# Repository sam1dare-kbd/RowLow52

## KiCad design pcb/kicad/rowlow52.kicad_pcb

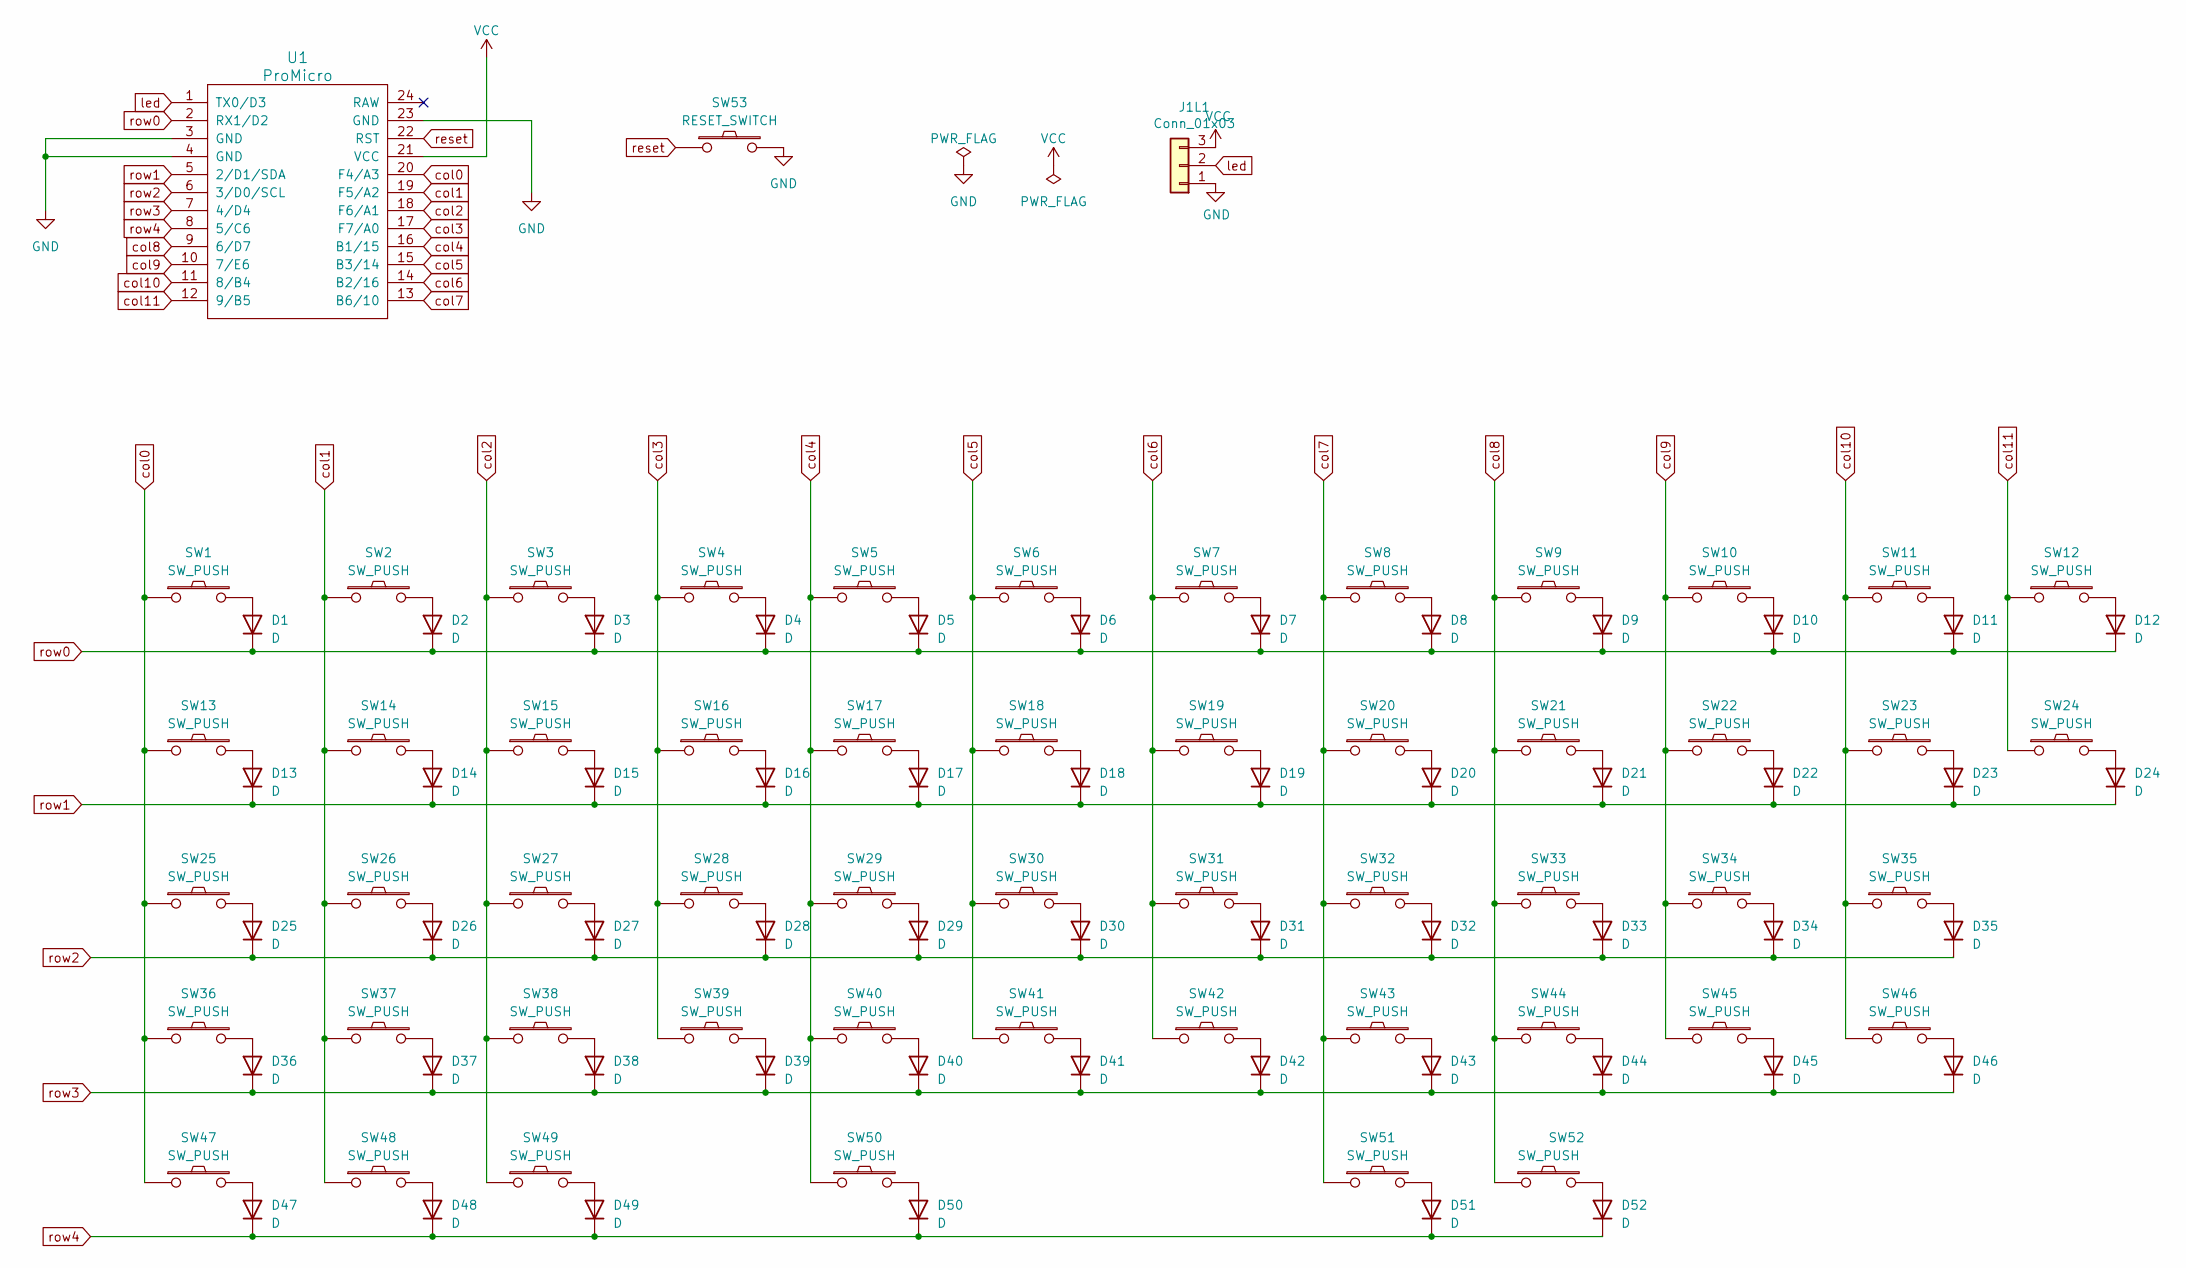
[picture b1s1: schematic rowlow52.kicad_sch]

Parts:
D1, D2, D3, D4, D5, D6, D7, D8, D9, D10, D11, D12, D13, D14, D15, D16, D17, D18, D19, D20, D21, D22, D23, D24, D25, D26, D27, D28, D29, D30, D31, D32, D33, D34, D35, D36, D37, D38, D39, D40, D41, D42, D43, D44, D45, D46, D47, D48, D49, D50, D51, D52: D; D3_TH_SMD
J1L1: Conn_01x03; StripLED_rev
SW1, SW2, SW3, SW4, SW5, SW6, SW7, SW8, SW9, SW10, SW11, SW14, SW15, SW16, SW17, SW18, SW19, SW20, SW21, SW22, SW23, SW24, SW26, SW27, SW28, SW29, SW30, SW31, SW32, SW33, SW34, SW37, SW38, SW39, SW40, SW41, SW42, SW43, SW44, SW45, SW48, SW49: SW_PUSH; CherryMX_Hotswap_1u
SW12, SW13, SW46, SW47, SW51: SW_PUSH; CherryMX_Hotswap_1.25u
SW25, SW52: SW_PUSH; CherryMX_Hotswap_1.5u
SW35: SW_PUSH; CherryMX_Hotswap_1.75u
SW36: SW_PUSH; CherryMX_Hotswap_2u
SW50: SW_PUSH; CherryMX_Hotswap_6.25u
SW53: RESET_SWITCH; ResetSW_1side
U1: ProMicro; ProMicro_v2_1side

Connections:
GND: J1L1.1, SW53.2, U1.3 (GND), U1.4 (GND), U1.23 (GND)
unnamed: D1.2 (A), SW1.2
unnamed: D2.2 (A), SW2.2
unnamed: D3.2 (A), SW3.2
unnamed: D4.2 (A), SW4.2
unnamed: D5.2 (A), SW5.2
unnamed: D6.2 (A), SW6.2
unnamed: D7.2 (A), SW7.2
unnamed: D8.2 (A), SW8.2
unnamed: D9.2 (A), SW9.2
unnamed: D10.2 (A), SW10.2
unnamed: D11.2 (A), SW11.2
unnamed: D12.2 (A), SW12.2
unnamed: D13.2 (A), SW13.2
unnamed: D14.2 (A), SW14.2
unnamed: D15.2 (A), SW15.2
unnamed: D16.2 (A), SW16.2
unnamed: D17.2 (A), SW17.2
unnamed: D18.2 (A), SW18.2
unnamed: D19.2 (A), SW19.2
unnamed: D20.2 (A), SW20.2
unnamed: D21.2 (A), SW21.2
unnamed: D22.2 (A), SW22.2
unnamed: D23.2 (A), SW23.2
unnamed: D24.2 (A), SW24.2
unnamed: D25.2 (A), SW25.2
unnamed: D26.2 (A), SW26.2
unnamed: D27.2 (A), SW27.2
unnamed: D28.2 (A), SW28.2
unnamed: D29.2 (A), SW29.2
unnamed: D30.2 (A), SW30.2
unnamed: D31.2 (A), SW31.2
unnamed: D32.2 (A), SW32.2
unnamed: D33.2 (A), SW33.2
unnamed: D34.2 (A), SW34.2
unnamed: D35.2 (A), SW35.2
unnamed: D36.2 (A), SW36.2
unnamed: D37.2 (A), SW37.2
unnamed: D38.2 (A), SW38.2
unnamed: D39.2 (A), SW39.2
unnamed: D40.2 (A), SW40.2
unnamed: D41.2 (A), SW41.2
unnamed: D42.2 (A), SW42.2
unnamed: D43.2 (A), SW43.2
unnamed: D44.2 (A), SW44.2
unnamed: D45.2 (A), SW45.2
unnamed: D46.2 (A), SW46.2
unnamed: D47.2 (A), SW47.2
unnamed: D48.2 (A), SW48.2
unnamed: D49.2 (A), SW49.2
unnamed: D50.2 (A), SW50.2
unnamed: D51.2 (A), SW51.2
unnamed: D52.2 (A), SW52.2
VCC: J1L1.3, U1.21 (VCC)
col0: SW1.1, SW13.1, SW25.1, SW36.1, SW47.1, U1.20 (F4/A3)
col1: SW2.1, SW14.1, SW26.1, SW37.1, SW48.1, U1.19 (F5/A2)
col2: SW3.1, SW15.1, SW27.1, SW38.1, SW49.1, U1.18 (F6/A1)
col3: SW4.1, SW16.1, SW28.1, SW39.1, U1.17 (F7/A0)
col4: SW5.1, SW17.1, SW29.1, SW40.1, SW50.1, U1.16 (B1/15)
col5: SW6.1, SW18.1, SW30.1, SW41.1, U1.15 (B3/14)
col6: SW7.1, SW19.1, SW31.1, SW42.1, U1.14 (B2/16)
col7: SW8.1, SW20.1, SW32.1, SW43.1, SW51.1, U1.13 (B6/10)
col8: SW9.1, SW21.1, SW33.1, SW44.1, SW52.1, U1.9 (6/D7)
col9: SW10.1, SW22.1, SW34.1, SW45.1, U1.10 (7/E6)
col10: SW11.1, SW23.1, SW35.1, SW46.1, U1.11 (8/B4)
col11: SW12.1, SW24.1, U1.12 (9/B5)
led: J1L1.2, U1.1 (TX0/D3)
reset: SW53.1, U1.22 (RST)
row0: D1.1 (K), D2.1 (K), D3.1 (K), D4.1 (K), D5.1 (K), D6.1 (K), D7.1 (K), D8.1 (K), D9.1 (K), D10.1 (K), D11.1 (K), D12.1 (K), U1.2 (RX1/D2)
row1: D13.1 (K), D14.1 (K), D15.1 (K), D16.1 (K), D17.1 (K), D18.1 (K), D19.1 (K), D20.1 (K), D21.1 (K), D22.1 (K), D23.1 (K), D24.1 (K), U1.5 (2/D1/SDA)
row2: D25.1 (K), D26.1 (K), D27.1 (K), D28.1 (K), D29.1 (K), D30.1 (K), D31.1 (K), D32.1 (K), D33.1 (K), D34.1 (K), D35.1 (K), U1.6 (3/D0/SCL)
row3: D36.1 (K), D37.1 (K), D38.1 (K), D39.1 (K), D40.1 (K), D41.1 (K), D42.1 (K), D43.1 (K), D44.1 (K), D45.1 (K), D46.1 (K), U1.7 (4/D4)
row4: D47.1 (K), D48.1 (K), D49.1 (K), D50.1 (K), D51.1 (K), D52.1 (K), U1.8 (5/C6)

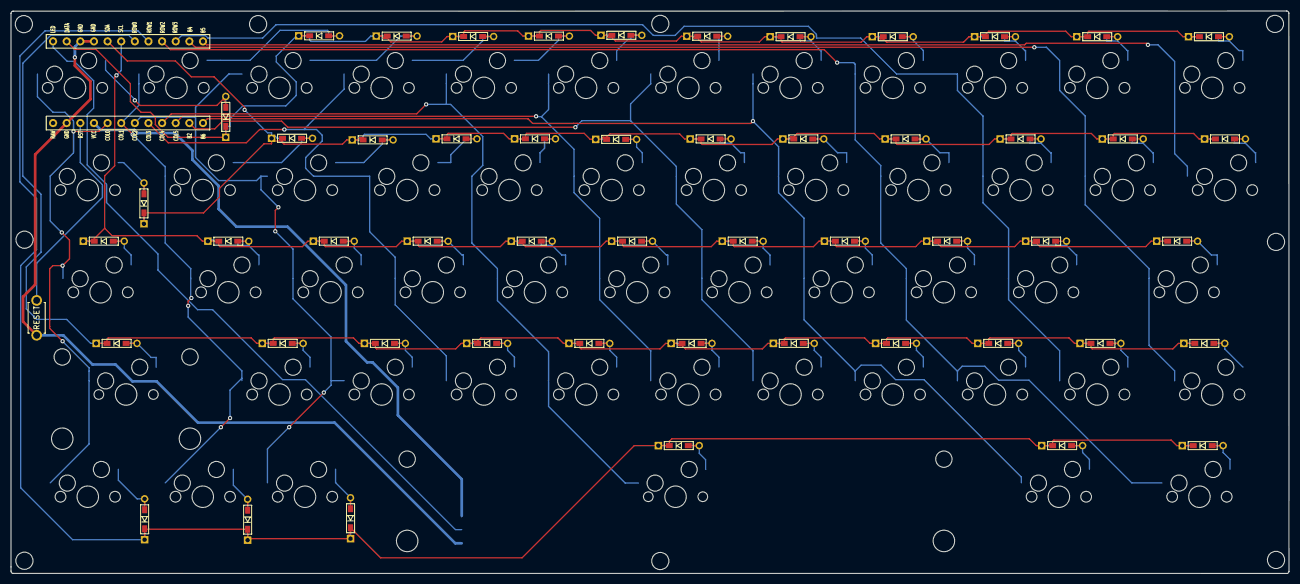
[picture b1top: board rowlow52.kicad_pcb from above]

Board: 2 copper layers, 238.2 x 104.8 mm, 116 parts (1 on the bottom side), 73 nets.

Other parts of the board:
Ref00, Ref01, Ref02, Ref03, Ref04, Ref05, Ref06, Ref07, Ref08: Val**; m3_Screw_Hole_EdgeCuts

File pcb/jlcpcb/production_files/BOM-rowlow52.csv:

Comment,Designator,Footprint,LCSC
SW_PUSH,SW23,CherryMX_Hotswap_1u,
D,D29,D3_TH_SMD,
D,D3,D3_TH_SMD,
D,D39,D3_TH_SMD,
SW_PUSH,SW3,CherryMX_Hotswap_1u,
D,D33,D3_TH_SMD,
D,D6,D3_TH_SMD,
SW_PUSH,SW8,CherryMX_Hotswap_1u,
SW_PUSH,SW39,CherryMX_Hotswap_1u,
D,D20,D3_TH_SMD,
D,D9,D3_TH_SMD,
D,D52,D3_TH_SMD,
SW_PUSH,SW32,CherryMX_Hotswap_1u,
D,D18,D3_TH_SMD,
D,D48,D3_TH_SMD,
SW_PUSH,SW35,CherryMX_Hotswap_1.75u,
D,D38,D3_TH_SMD,
SW_PUSH,SW6,CherryMX_Hotswap_1u,
D,D24,D3_TH_SMD,
SW_PUSH,SW19,CherryMX_Hotswap_1u,
D,D45,D3_TH_SMD,
SW_PUSH,SW43,CherryMX_Hotswap_1u,
D,D40,D3_TH_SMD,
SW_PUSH,SW30,CherryMX_Hotswap_1u,
D,D23,D3_TH_SMD,
SW_PUSH,SW13,CherryMX_Hotswap_1.25u,
SW_PUSH,SW28,CherryMX_Hotswap_1u,
D,D43,D3_TH_SMD,
SW_PUSH,SW42,CherryMX_Hotswap_1u,
D,D46,D3_TH_SMD,
SW_PUSH,SW16,CherryMX_Hotswap_1u,
SW_PUSH,SW15,CherryMX_Hotswap_1u,
SW_PUSH,SW41,CherryMX_Hotswap_1u,
SW_PUSH,SW44,CherryMX_Hotswap_1u,
SW_PUSH,SW47,CherryMX_Hotswap_1.25u,
SW_PUSH,SW4,CherryMX_Hotswap_1u,
SW_PUSH,SW40,CherryMX_Hotswap_1u,
SW_PUSH,SW50,CherryMX_Hotswap_6.25u,
SW_PUSH,SW22,CherryMX_Hotswap_1u,
SW_PUSH,SW27,CherryMX_Hotswap_1u,
D,D28,D3_TH_SMD,
SW_PUSH,SW52,CherryMX_Hotswap_1.5u,
SW_PUSH,SW24,CherryMX_Hotswap_1u,
SW_PUSH,SW37,CherryMX_Hotswap_1u,
D,D4,D3_TH_SMD,
SW_PUSH,SW20,CherryMX_Hotswap_1u,
D,D14,D3_TH_SMD,
SW_PUSH,SW2,CherryMX_Hotswap_1u,
D,D10,D3_TH_SMD,
D,D41,D3_TH_SMD,
D,D1,D3_TH_SMD,
SW_PUSH,SW1,CherryMX_Hotswap_1u,
SW_PUSH,SW12,CherryMX_Hotswap_1.25u,
D,D51,D3_TH_SMD,
SW_PUSH,SW49,CherryMX_Hotswap_1u,
D,D34,D3_TH_SMD,
D,D15,D3_TH_SMD,
D,D2,D3_TH_SMD,
D,D27,D3_TH_SMD,
SW_PUSH,SW17,CherryMX_Hotswap_1u,
SW_PUSH,SW21,CherryMX_Hotswap_1u,
D,D25,D3_TH_SMD,
SW_PUSH,SW5,CherryMX_Hotswap_1u,
D,D12,D3_TH_SMD,
D,D21,D3_TH_SMD,
RESET_SWITCH,SW53,ResetSW_1side,
SW_PUSH,SW29,CherryMX_Hotswap_1u,
SW_PUSH,SW26,CherryMX_Hotswap_1u,
D,D16,D3_TH_SMD,
D,D7,D3_TH_SMD,
SW_PUSH,SW25,CherryMX_Hotswap_1.5u,
SW_PUSH,SW36,CherryMX_Hotswap_2u,
D,D22,D3_TH_SMD,
D,D36,D3_TH_SMD,
D,D50,D3_TH_SMD,
D,D8,D3_TH_SMD,
SW_PUSH,SW51,CherryMX_Hotswap_1.25u,
D,D35,D3_TH_SMD,
D,D11,D3_TH_SMD,
SW_PUSH,SW7,CherryMX_Hotswap_1u,
D,D32,D3_TH_SMD,
SW_PUSH,SW18,CherryMX_Hotswap_1u,
SW_PUSH,SW14,CherryMX_Hotswap_1u,
SW_PUSH,SW33,CherryMX_Hotswap_1u,
D,D26,D3_TH_SMD,
SW_PUSH,SW48,CherryMX_Hotswap_1u,
D,D17,D3_TH_SMD,
D,D19,D3_TH_SMD,
D,D31,D3_TH_SMD,
SW_PUSH,SW11,CherryMX_Hotswap_1u,
SW_PUSH,SW34,CherryMX_Hotswap_1u,
D,D49,D3_TH_SMD,
SW_PUSH,SW45,CherryMX_Hotswap_1u,
D,D47,D3_TH_SMD,
SW_PUSH,SW38,CherryMX_Hotswap_1u,
SW_PUSH,SW46,CherryMX_Hotswap_1.25u,
D,D42,D3_TH_SMD,
SW_PUSH,SW9,CherryMX_Hotswap_1u,
D,D44,D3_TH_SMD,
SW_PUSH,SW10,CherryMX_Hotswap_1u,
D,D5,D3_TH_SMD,
SW_PUSH,SW31,CherryMX_Hotswap_1u,
ProMicro,U1,ProMicro_v2_1side,
D,D37,D3_TH_SMD,
D,D30,D3_TH_SMD,
D,D13,D3_TH_SMD,
Conn_01x03,J1L1,StripLED_1side,

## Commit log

2024-09-06 Update LICENSE
